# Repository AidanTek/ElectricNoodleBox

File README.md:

# ElectricNoodleBox
Open Source Hardware from/with Electric Noodle Box

This repository hosts a number of hardware projects that are at various stages of completion, for documentation and further info, please visit this page - [Modular Series Overview](https://electricnoodlebox.com/tutorials/modular-series-overview/). Generally speaking, if the docs don't exist then the project probably isn't ready to go! I welcome comments from anyone, whether you are starting out and need better supporting docs, or you are an experienced engineer and think my designs are awful! ;) 

The Electric Noodle Box Modular Series circuits are [open source hardware](https://www.oshwa.org/definition/) designs released under the [CERN-OSH-W](https://ohwr.org/cern_ohl_w_v2.txt) license. The aim is to help you learn how to build electronic instruments, and to make building more accessible. I chose to release designs this way in recognition of my own learning, made possible by the rich history of DIY sound electronics available in the public domain. Open source hardware allows for continued dialogue in making and inventing and I want you to be able to take part in the conversation, whatever point you are at in your learning journey.

All hardware files are produced in Eagle. The free version of Eagle will allow you to browse, modify (most designs, there are some limitations) and create GERBERs for production - PCB fabs such as [OSHPark](https://oshpark.com/) will take Eagle files directly. I have also provided the ENB Eagle library to maintain parts that might not be included in the standard libraries. Please let me know by raising an issue if you have any problems accessing or opening these files.

I recognise there are some issues with Eagle and open-source due to the limitations of the free version. I believe it is possible to convert Eagle .brd .sch and .lbr files over to KiCAD - but this is a big task. I would welcome support if someone has experience and wants to take this on.

## License

The CERN-OSH-W allows you to use all source files in this repository in any way you wish. It requires that any resources you use from here remain as open source, even if used in a wider project that is otherwise closed. 

I chose this license so you are not restricted in your use of the source contentno matter what your plans are. I am interested in what you do with these designs however as I want them to stimulate learning and dialogue. My personal request is that you consider sharing ideas if choose to make, modify or integrate content from this source, and consider referencing me or Electric Noodle Box for the many hours I have spent developing this resource! :)

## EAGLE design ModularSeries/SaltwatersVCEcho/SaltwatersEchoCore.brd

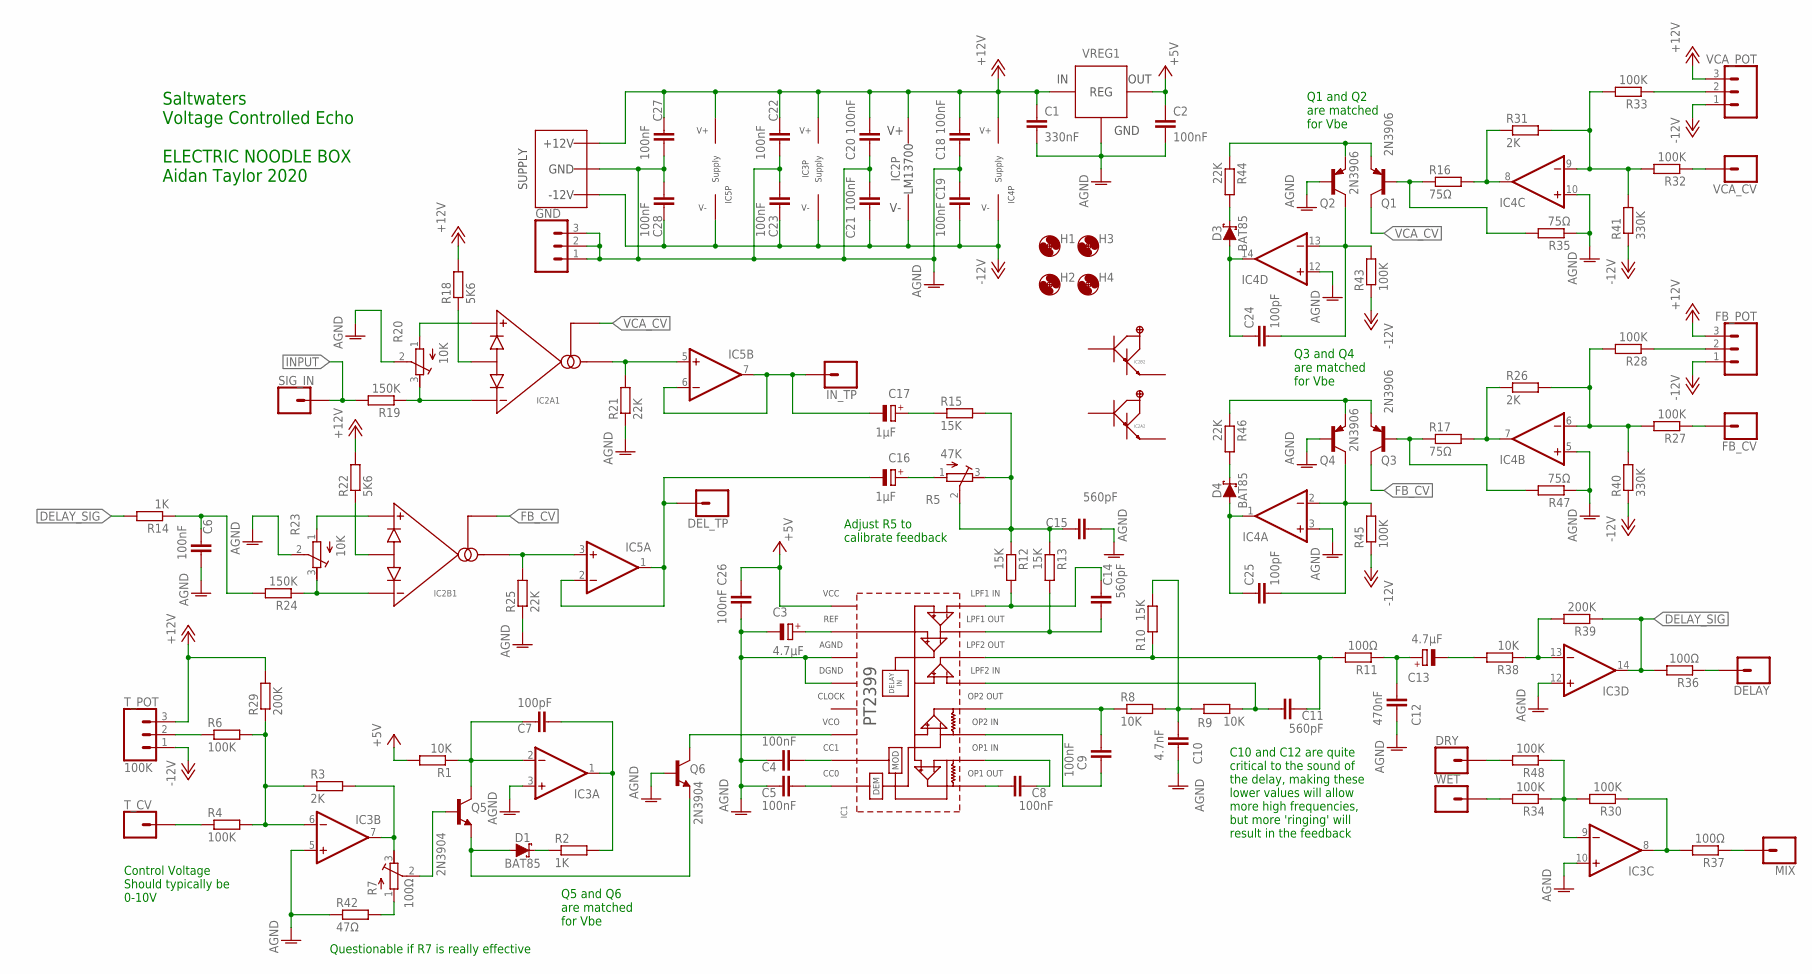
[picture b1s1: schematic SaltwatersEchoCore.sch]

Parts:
C1: 330nF; C050-025X075
C2, C4, C5, C6, C8, C9, C18, C19, C20, C21, C22, C23, C26, C27, C28: 100nF; C050-025X075
C3, C13: 4.7µF; E2-5
C7, C24, C25: 100pF; C050-025X075
C10: 4.7nF; C050-025X075
C11, C14, C15: 560pF; C050-025X075
C12: 470nF; C050-025X075
C16, C17: 1µF; E2-5
D1, D3, D4: BAT85; DO35-7
DELAY: 1XWIREPAD; 1X01
DEL_TP: 1XWIREPAD; 1X01
DRY: 1XWIREPAD; 1X01
FB_CV: 1XWIREPAD; 1X01
FB_POT: 3XWIREPAD; 1X03
GND: 3XWIREPAD; 1X03
H1, H2, H3, H4: MOUNT-HOLE3.2; 3,2
IC1: PT2399DIL16; DIL16
IC2: LM13700DIL; DIL16
IC3, IC4: TL0X4DIL; DIL14
IC5: TL0X2DIL; DIL08
IN_TP: 1XWIREPAD; 1X01
MIX: 1XWIREPAD; 1X01
Q1, Q2, Q3, Q4: 2N3906; TO92
Q5, Q6: 2N3904; TO92
R1, R8, R9, R38: 10K; 0207/10
R2, R14: 1K; 0207/10
R3, R26, R31: 2K; 0207/10
R4, R6, R27, R28, R30, R32, R33, R34, R43, R45, R48: 100K; 0207/10
R5: 47K; RTRIM3296W
R7: 100Ω; RTRIM3296W
R10, R12, R13, R15: 15K; 0207/10
R11, R36, R37: 100Ω; 0207/10
R16, R17, R35, R47: 75Ω; 0207/10
R18, R22: 5K6; 0207/10
R19, R24: 150K; 0207/10
R20, R23: 10K; RTRIM3296W
R21, R25, R44, R46: 22K; 0207/10
R29, R39: 200K; 0207/10
R40, R41: 330K; 0207/10
R42: 47Ω; 0207/10
SIG_IN: 1XWIREPAD; 1X01
T_CV: 1XWIREPAD; 1X01
T_POT: 100K; 1X03
VCA_CV: 1XWIREPAD; 1X01
VCA_POT: 3XWIREPAD; 1X03
VREG1: L78L05TO92; TO92
WET: 1XWIREPAD; 1X01
WP1: COMBO_SUPPLY_HEADER; COMBINED_POWER

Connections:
+5V: C2.1, C26.1, IC1.1 (VCC), R1.2, VREG1.1 (VOUT)
+12V: C1.1, C18.2, C20.2, C22.2, C27.2, FB_POT.3, IC2.11 (V+), IC3.4 (V+), IC4.4 (V+), IC5.8 (V+), R18.2, R22.2, R29.2, T_POT.3, VCA_POT.3, VREG1.3 (VIN), WP1.V+1 (V++), WP1.V+2 (V++), WP1.V+3 (V++)
-12V: C19.1, C21.1, C23.1, C28.1, FB_POT.1, IC2.6 (V-), IC3.11 (V-), IC4.11 (V-), IC5.4 (V-), R40.1, R41.1, R43.1, R45.1, T_POT.1, VCA_POT.1, WP1.V-1 (V--), WP1.V-2 (V--), WP1.V-3 (V--)
AGND: C1.2, C2.2, C3.-, C4.2, C5.2, C6.2, C10.1, C12.1, C15.2, C18.1, C19.2, C20.1, C21.2, C22.1, C23.2, C26.2, C27.1, C28.2, GND.1, GND.2, GND.3, IC1.3 (AGND), IC1.4 (DGND), IC3.3 (+IN), IC3.5 (+IN), IC3.10 (+IN), IC3.12 (+IN), IC4.3 (+IN), IC4.5 (+IN), IC4.10 (+IN), IC4.12 (+IN), Q2.2 (B), Q4.2 (B), Q6.2 (B), R20.2 (S), R21.1, R23.2 (S), R25.1, R35.1, R42.1, R47.1, VREG1.2 (GND), WP1.GND1 (AGND), WP1.GND2 (AGND), WP1.GND3 (AGND), WP1.GND4 (AGND), WP1.GND5 (AGND), WP1.GND6 (AGND), WP1.GND7 (AGND), WP1.GND8 (AGND)
DELAY_SIG: IC3.14 (OUT), R14.2, R36.2, R39.1
FB_CV: IC2.16 (AMPBIAS), Q3.1 (C)
FB_RTN: C16.-, DEL_TP.1, IC5.1 (OUT), IC5.2 (-IN)
INPUT: R19.2, SIG_IN.1
unnamed: C3.+, IC1.2 (REF)
unnamed: C4.1, IC1.7 (CC1)
unnamed: C5.1, IC1.8 (CC0)
unnamed: IC1.6 (VCO), Q6.1 (C)
unnamed: C7.2, IC3.2 (-IN), Q5.1 (C), R1.1
unnamed: C7.1, IC3.1 (OUT), R2.2
unnamed: D1.A, Q5.3 (E), Q6.3 (E)
unnamed: C6.1, R14.1, R24.2
unnamed: D1.C, R2.1
unnamed: IC3.7 (OUT), R3.2, R7.3 (E)
unnamed: Q5.2 (B), R7.2 (S)
unnamed: R4.1, T_CV.1
unnamed: IC3.6 (-IN), R3.1, R4.2, R6.2, R29.1
unnamed: R6.1, T_POT.2
unnamed: C8.1, IC1.10 (OP1_IN)
unnamed: C8.2, IC1.9 (OP1_OUT)
unnamed: C9.1, IC1.11 (OP2_IN)
unnamed: C9.2, IC1.12 (OP2_OUT), R8.1
unnamed: C10.2, R8.2, R9.2, R10.1
unnamed: C11.2, IC1.13 (LPF2_IN), R9.1
unnamed: C11.1, IC1.14 (LPF2_OUT), R10.2, R11.2
unnamed: Q1.2 (B), R16.1, R35.2
unnamed: C12.2, C13.+, R11.1
unnamed: C14.1, IC1.16 (LPF1_IN), R12.2
unnamed: C14.2, IC1.15 (LPF1_OUT), R13.2
unnamed: C15.1, R5.2 (S), R5.3 (E), R12.1, R13.1, R15.2
unnamed: C17.+, R15.1
unnamed: C16.+, R5.1 (A)
unnamed: IC2.4 (AMP-), R19.1, R20.3 (E)
unnamed: IC2.3 (AMP+), R20.1 (A)
unnamed: IC4.7 (OUT), R17.2, R26.1
unnamed: IC2.2 (DIODES), R18.1
unnamed: IC2.5 (AMPOUT), IC5.5 (+IN), R21.2
unnamed: C17.-, IC5.6 (-IN), IC5.7 (OUT), IN_TP.1
unnamed: DELAY.1, R36.1
unnamed: IC2.15 (DIODES), R22.1
unnamed: IC2.13 (AMP-), R23.3 (E), R24.1
unnamed: IC2.14 (AMP+), R23.1 (A)
unnamed: IC4.6 (-IN), R26.2, R27.2, R28.2, R40.2
unnamed: IC2.12 (AMPOUT), IC5.3 (+IN), R25.2
unnamed: Q3.2 (B), R17.1, R47.2
unnamed: DRY.1, R48.2
unnamed: FB_CV.1, R27.1
unnamed: IC4.8 (OUT), R16.2, R31.1
unnamed: FB_POT.2, R28.1
unnamed: IC4.9 (-IN), R31.2, R32.2, R33.2, R41.2
unnamed: C24.1, D3.A, IC4.14 (OUT)
unnamed: C24.2, IC4.13 (-IN), Q2.1 (C), R43.2
unnamed: R32.1, VCA_CV.1
unnamed: R33.1, VCA_POT.2
unnamed: C13.-, R38.2
unnamed: R34.2, WET.1
unnamed: MIX.1, R37.1
unnamed: R7.1 (A), R42.2
unnamed: IC3.9 (-IN), R30.2, R34.1, R48.1
unnamed: IC3.8 (OUT), R30.1, R37.2
unnamed: D3.C, R44.2
unnamed: Q1.3 (E), Q2.3 (E), R44.1
unnamed: IC3.13 (-IN), R38.1, R39.2
unnamed: C25.2, IC4.2 (-IN), Q4.1 (C), R45.2
unnamed: C25.1, D4.A, IC4.1 (OUT)
unnamed: D4.C, R46.2
unnamed: Q3.3 (E), Q4.3 (E), R46.1
VCA_CV: IC2.1 (AMPBIAS), Q1.1 (C)

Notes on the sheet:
Control Voltage Should typically be 0-10V
Saltwaters Voltage Controlled Echo ELECTRIC NOODLE BOX Aidan Taylor 2020
Q1 and Q2 are matched for Vbe
Q3 and Q4 are matched for Vbe
Q5 and Q6 are matched for Vbe
Adjust R5 to calibrate feedback
Questionable if R7 is really effective
C10 and C12 are quite critical to the sound of the delay, making these lower values will allow more high frequencies, but more 'ringing' will result in the feedback

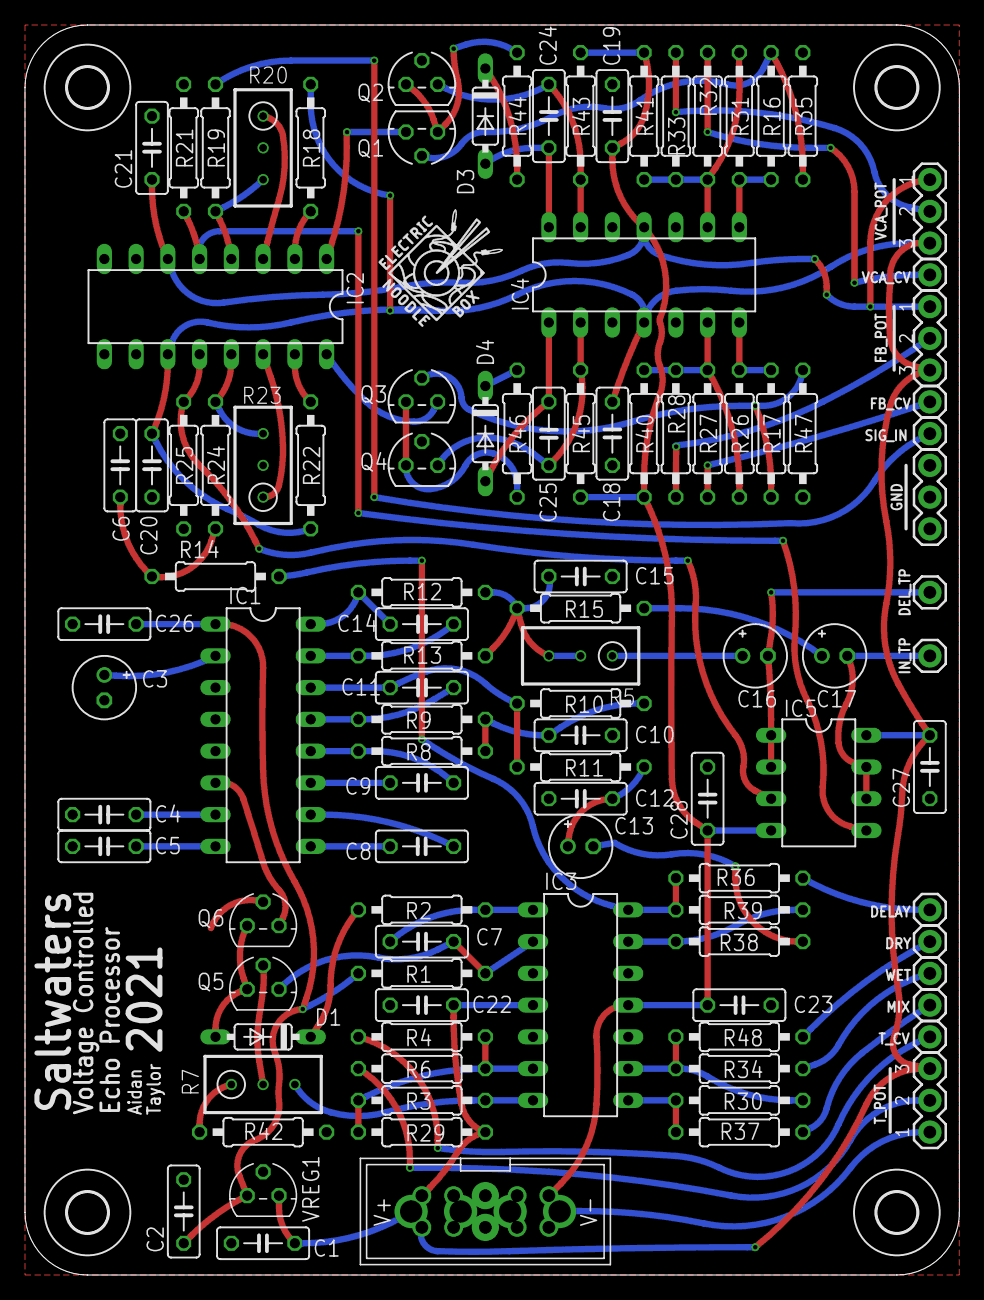
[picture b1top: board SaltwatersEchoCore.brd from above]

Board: 2 copper layers, 74.8 x 100.0 mm, 112 parts (1 on the bottom side), 72 nets.

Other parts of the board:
U$1, U$2: LOGO10X10

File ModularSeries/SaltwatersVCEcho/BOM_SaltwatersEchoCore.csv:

Qty,Value,Package,Parts,Description,RETAILER,CATALOGUE
,,,,,,
9,100K,0207/10,"R4, R5, R6, R27, R28, R32, R33, R43, R45","RESISTOR, European symbol",Farnell,2329853
5,100Ω,0207/10,"R30, R34, R36, R37, R48","RESISTOR, European symbol",Farnell,2329854
5,10K,0207/10,"R8, R9, R35, R38, R47","RESISTOR, European symbol",Farnell,2329855
2,150K,0207/10,"R19, R24","RESISTOR, European symbol",Farnell,2329871
5,15K,0207/10,"R10, R12, R13, R14, R15","RESISTOR, European symbol",Farnell,2329873
3,1K,0207/10,"R2, R16, R17","RESISTOR, European symbol",Farnell,2329885
2,200K,0207/10,"R29, R39","RESISTOR, European symbol",Farnell,2329895
4,22K,0207/10,"R21, R25, R44, R46","RESISTOR, European symbol",Farnell,2329901
3,2K,0207/10,"R3, R26, R31","RESISTOR, European symbol",Farnell,2329911
2,330K,0207/10,"R40, R41","RESISTOR, European symbol",Farnell,9341765
1,47K,0207/10,R1,"RESISTOR, European symbol",Farnell,2329944
1,47Ω,0207/10,R42,"RESISTOR, European symbol",Farnell,2329945
2,5K7,0207/10,"R18, R22","RESISTOR, European symbol",Farnell,2329958
1,7K5,0207/10,R11,"RESISTOR, European symbol",Farnell,2329974
1,100Ω,RTRIM3296W,R7,Trimm resistor,Farnell,9353500
2,10K,RTRIM3296W,"R20, R23",Trimm resistor,Farnell,9353186
,,,,,,
14,100nF,C050-025X075,"C2, C4, C5, C8, C9, C18, C19, C20, C21, C22, C23, C26, C27, C28","CAPACITOR, European symbol",Farnell,2797801
3,100pF,C050-025X075,"C7, C24, C25","CAPACITOR, European symbol",Farnell,1141765
1,10nF,C050-025X075,C12,"CAPACITOR, European symbol",Farnell,1141772
1,330nF,C050-025X075,C1,"CAPACITOR, European symbol",Farnell,2309021
1,4.7nF,C050-025X075,C10,"CAPACITOR, European symbol",Farnell,2860131
2,4.7µF,E2-5,"C3, C13","POLARIZED CAPACITOR, European symbol",Farnell,9451234
3,560pF,C050-025X075,"C11, C14, C15","CAPACITOR, European symbol",Farnell,2990777
3,1µF,E2-5,"C6, C16, C17","POLARIZED CAPACITOR, European symbol",Farnell,1870979
,,,,,,
1,L78L05,TO92,VREG1,5V Regulator TO-92,Farnell,3335817
2,2N3904,TO92,"Q5, Q6",NPN TRANSISTOR,Farnell,1574370
4,2N3906,TO92,"Q1, Q2, Q3, Q4",PNP Transistor,Farnell,1574372
4,BAT85,DO35-7,"D1, D2, D3, D4",BAT85 Schottky Diode,Farnell,2889133
1,LM13700,DIL16,IC2,Dual Transconductance Amplifier with Darlington Buffer,Farnell,3118206
1,TL082,DIL08,IC5,Dual Operational Amplifier,Farnell,1103189
2,TL084,DIL14,"IC3, IC4",Quad Operational Amplifier,Farnell,3117825
1,PT2399DIL16,DIL16,IC1,Echo Processor DIP,Tayda,A-043
,,,,,,
3,Pin Header,Pin Header,,8way 1row 2.54mm Header Pin,Farnell,2856626
1,Power Header,,WP1,10 way Shrouded IDC,Farnell,2843527
,,,,,,
3,B100K,,"T_POT, FB_POT, VCA_POT",Taiwan Alpha 16mm (panel part),Rapid,65-0756
2,B10K,,"T_CV, FB_CV",Taiwan Alpha 16mm (panel part),Rapid,65-0753
6,Banana or Jack Patch Point,1X01,"DELAY, FB_CV, MIX, SIG_IN, T_CV, VCA_CV",Banana or Jack patch point (panel part),Farnell,1698951

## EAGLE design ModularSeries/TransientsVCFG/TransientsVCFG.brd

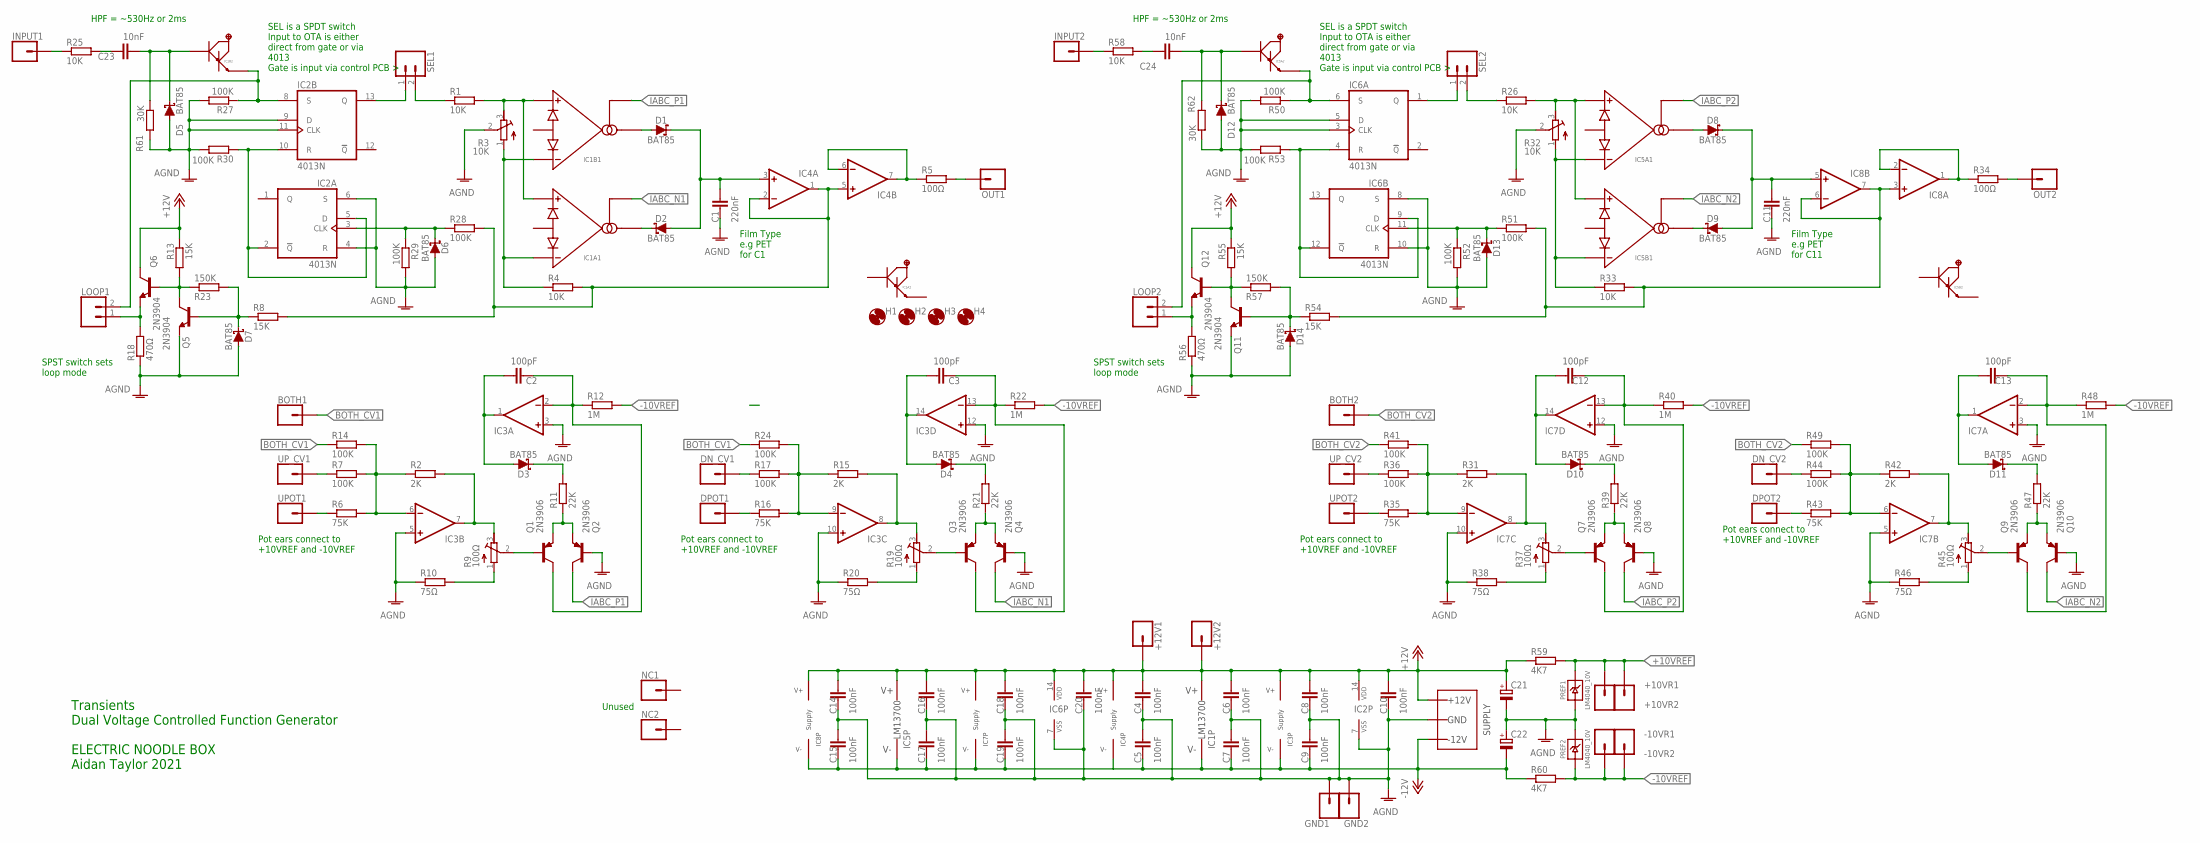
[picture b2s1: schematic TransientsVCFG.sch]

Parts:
+10VR1, +10VR2, +12V1, +12V2: 1XWIREPAD; 1X01
-10VR1, -10VR2: 1XWIREPAD; 1X01
BOTH1, BOTH2: 1XWIREPAD; 1X01
C1, C11: 220nF; C050-025X075
C2, C3, C12, C13: 100pF; C050-025X075
C4, C5, C6, C7, C8, C9, C10, C14, C15, C16, C17, C18, C19, C20: 100nF; C050-025X075
C21, C22: CPOL-EUE2.5-6; E2,5-6
C23, C24: 10nF; C050-025X075
D1, D2, D3, D4, D5, D6, D7, D8, D9, D10, D11, D12, D13, D14: BAT85; DO35-7
DN_CV1, DN_CV2: 1XWIREPAD; 1X01
DPOT1, DPOT2: 1XWIREPAD; 1X01
GND1, GND2: 1XWIREPAD; 1X01
H1, H2, H3, H4: MOUNT-HOLE3.2; 3,2
IC1, IC5: LM13700DIL; DIL16
IC2, IC6: 4013N; DIL14
IC3, IC7: TL0X4DIL; DIL14
IC4, IC8: TL0X2DIL; DIL08
INPUT1, INPUT2: 1XWIREPAD; 1X01
LOOP1, LOOP2: 2XWIREPAD; 1X02
NC1, NC2: 1XWIREPAD; 1X01
OUT1, OUT2: 1XWIREPAD; 1X01
PREF1, PREF2: LM4040_10V; TO92
Q1, Q2, Q3, Q4, Q7, Q8, Q9, Q10: 2N3906; TO92
Q5, Q6, Q11, Q12: 2N3904; TO92
R1, R4, R25, R26, R33, R58: 10K; 0207/10
R2, R15, R31, R42: 2K; 0207/10
R3, R32: 10K; RTRIM3296W
R5, R34: 100Ω; 0207/10
R6, R16, R35, R43: 75K; 0207/10
R7, R14, R17, R24, R27, R28, R29, R30, R36, R41, R44, R49, R50, R51, R52, R53: 100K; 0207/10
R8, R13, R54, R55: 15K; 0207/10
R9, R19, R37, R45: 100Ω; RTRIM3296W
R10, R20, R38, R46: 75Ω; 0207/10
R11, R21, R39, R47: 22K; 0207/10
R12, R22, R40, R48: 1M; 0207/10
R18, R56: 470Ω; 0207/10
R23, R57: 150K; 0207/10
R59, R60: 4K7; 0207/10
R61, R62: 30K; 0207/10
SEL1, SEL2: 2XWIREPAD; 1X02
UPOT1, UPOT2: 1XWIREPAD; 1X01
UP_CV1, UP_CV2: 1XWIREPAD; 1X01
WP1: COMBO_SUPPLY_HEADER; COMBINED_POWER

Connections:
+10VREF: +10VR1.1, +10VR2.1, PREF1.2 (CATHODE), R59.2
+12V: +12V1.1, +12V2.1, C4.1, C6.1, C8.1, C10.1, C14.1, C16.1, C18.1, C20.1, C21.+, IC1.11 (V+), IC2.14 (VDD), IC3.4 (V+), IC4.8 (V+), IC5.11 (V+), IC6.14 (VDD), IC7.4 (V+), IC8.8 (V+), Q6.1 (C), Q12.1 (C), R13.1, R55.1, R59.1, WP1.V+1 (V++), WP1.V+2 (V++), WP1.V+3 (V++)
-10VREF: -10VR1.1, -10VR2.1, PREF2.3 (ANODE), R12.2, R22.2, R40.2, R48.2, R60.2
-12V: C5.2, C7.2, C9.2, C15.2, C17.2, C19.2, C22.-, IC1.6 (V-), IC3.11 (V-), IC4.4 (V-), IC5.6 (V-), IC7.11 (V-), IC8.4 (V-), R60.1, WP1.V-1 (V--), WP1.V-2 (V--), WP1.V-3 (V--)
AGND: C1.2, C4.2, C5.1, C6.2, C7.1, C8.2, C9.1, C10.2, C11.2, C14.2, C15.1, C16.2, C17.1, C18.2, C19.1, C20.2, C21.-, C22.+, D5.A, D6.A, D7.A, D12.A, D13.A, D14.A, GND1.1, GND2.1, IC2.4 (R), IC2.6 (S), IC2.7 (VSS), IC2.9 (D), IC2.11 (CLK), IC3.3 (+IN), IC3.5 (+IN), IC3.10 (+IN), IC3.12 (+IN), IC6.3 (CLK), IC6.5 (D), IC6.7 (VSS), IC6.8 (S), IC6.10 (R), IC7.3 (+IN), IC7.5 (+IN), IC7.10 (+IN), IC7.12 (+IN), PREF1.3 (ANODE), PREF2.2 (CATHODE), Q2.2 (B), Q4.2 (B), Q5.3 (E), Q8.2 (B), Q10.2 (B), Q11.3 (E), R3.2 (S), R10.1, R18.1, R20.1, R27.2, R29.2, R30.2, R32.2 (S), R38.1, R46.1, R50.2, R52.2, R53.2, R56.1, R61.2, R62.2, WP1.GND1 (AGND), WP1.GND2 (AGND), WP1.GND3 (AGND), WP1.GND4 (AGND), WP1.GND5 (AGND), WP1.GND6 (AGND), WP1.GND7 (AGND), WP1.GND8 (AGND)
BOTH_CV1: BOTH1.1, R14.1, R24.1
BOTH_CV2: BOTH2.1, R41.1, R49.1
IABC_N1: IC1.1 (AMPBIAS), Q4.1 (C)
IABC_N2: IC5.16 (AMPBIAS), Q10.1 (C)
IABC_P1: IC1.16 (AMPBIAS), Q2.1 (C)
IABC_P2: IC5.1 (AMPBIAS), Q8.1 (C)
unnamed: IC1.3 (AMP+), IC1.14 (AMP+), R1.2, R3.3 (E)
unnamed: D1.A, IC1.12 (AMPOUT)
unnamed: C1.1, D1.C, D2.A, IC4.3 (+IN)
unnamed: IC4.1 (OUT), IC4.2 (-IN), IC4.5 (+IN), R4.2, R8.2, R28.2
unnamed: D2.C, IC1.5 (AMPOUT)
unnamed: IC4.6 (-IN), IC4.7 (OUT), R5.1
unnamed: IC1.4 (AMP-), IC1.13 (AMP-), R3.1 (A), R4.1
unnamed: IC3.6 (-IN), R2.1, R6.2, R7.2, R14.2
unnamed: IC3.7 (OUT), R2.2, R9.3 (E)
unnamed: R9.1 (A), R10.2
unnamed: Q1.2 (B), R9.2 (S)
unnamed: Q1.3 (E), Q2.3 (E), R11.1
unnamed: C2.1, D3.A, IC3.1 (OUT)
unnamed: C2.2, IC3.2 (-IN), Q1.1 (C), R12.1
unnamed: D3.C, R11.2
unnamed: IC5.3 (AMP+), IC5.14 (AMP+), R26.2, R32.3 (E)
unnamed: C11.1, D8.C, D9.A, IC8.5 (+IN)
unnamed: R7.1, UP_CV1.1
unnamed: OUT1.1, R5.2
unnamed: IC3.9 (-IN), R15.1, R16.2, R17.2, R24.2
unnamed: R6.1, UPOT1.1
unnamed: IC3.8 (OUT), R15.2, R19.3 (E)
unnamed: R19.1 (A), R20.2
unnamed: Q3.2 (B), R19.2 (S)
unnamed: Q3.3 (E), Q4.3 (E), R21.1
unnamed: C3.1, D4.A, IC3.14 (OUT)
unnamed: C3.2, IC3.13 (-IN), Q3.1 (C), R22.1
unnamed: IC1.9 (BUFF_OUT), IC2.8 (S), LOOP1.2, R27.1
unnamed: D4.C, R21.2
unnamed: Q5.1 (C), Q6.2 (B), R13.2, R23.1
unnamed: DN_CV1.1, R17.1
unnamed: DPOT1.1, R16.1
unnamed: R1.1, SEL1.2
unnamed: IC2.13 (Q), SEL1.1
unnamed: IC8.3 (+IN), IC8.6 (-IN), IC8.7 (OUT), R33.2, R51.2, R54.2
unnamed: INPUT1.1, R25.1
unnamed: IC2.2 (!Q), IC2.5 (D), IC2.10 (R), R30.1
unnamed: LOOP1.1, Q6.3 (E), R18.2
unnamed: D7.C, Q5.2 (B), R8.1, R23.2
unnamed: C23.2, D5.C, IC1.10 (BUFF_IN), R61.1
unnamed: D6.C, IC2.3 (CLK), R28.1, R29.1
unnamed: D8.A, IC5.5 (AMPOUT)
unnamed: D9.C, IC5.12 (AMPOUT)
unnamed: IC5.4 (AMP-), IC5.13 (AMP-), R32.1 (A), R33.1
unnamed: IC8.1 (OUT), IC8.2 (-IN), R34.1
unnamed: IC7.9 (-IN), R31.1, R35.2, R36.2, R41.2
unnamed: IC7.8 (OUT), R31.2, R37.3 (E)
unnamed: R37.1 (A), R38.2
unnamed: Q7.2 (B), R37.2 (S)
unnamed: Q7.3 (E), Q8.3 (E), R39.1
unnamed: C12.1, D10.A, IC7.14 (OUT)
unnamed: C12.2, IC7.13 (-IN), Q7.1 (C), R40.1
unnamed: R36.1, UP_CV2.1
unnamed: R35.1, UPOT2.1
unnamed: OUT2.1, R34.2
unnamed: IC7.6 (-IN), R42.1, R43.2, R44.2, R49.2
unnamed: IC7.7 (OUT), R42.2, R45.3 (E)
unnamed: R45.1 (A), R46.2
unnamed: Q9.2 (B), R45.2 (S)
unnamed: Q9.3 (E), Q10.3 (E), R47.1
unnamed: C13.1, D11.A, IC7.1 (OUT)
unnamed: C13.2, IC7.2 (-IN), Q9.1 (C), R48.1
unnamed: DN_CV2.1, R44.1
unnamed: DPOT2.1, R43.1
unnamed: IC6.4 (R), IC6.9 (D), IC6.12 (!Q), R53.1
unnamed: IC5.8 (BUFF_OUT), IC6.6 (S), LOOP2.2, R50.1
unnamed: R26.1, SEL2.2
unnamed: IC6.1 (Q), SEL2.1
unnamed: D13.C, IC6.11 (CLK), R51.1, R52.1
unnamed: C24.1, R58.2
unnamed: D11.C, R47.2
unnamed: D10.C, R39.2
unnamed: Q11.1 (C), Q12.2 (B), R55.2, R57.1
unnamed: LOOP2.1, Q12.3 (E), R56.2
unnamed: D14.C, Q11.2 (B), R54.1, R57.2
unnamed: INPUT2.1, R58.1
unnamed: C23.1, R25.2
unnamed: C24.2, D12.C, IC5.7 (BUFF_IN), R62.1

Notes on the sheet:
Film Type e.g PET for C1
SEL is a SPDT switch Input to OTA is either direct from gate or via 4013 Gate is input via control PCB >
SPST switch sets loop mode
Film Type e.g PET for C11
Pot ears connect to +10VREF and -10VREF
Unused
HPF = ~530Hz or 2ms
Transients Dual Voltage Controlled Function Generator ELECTRIC NOODLE BOX Aidan Taylor 2021

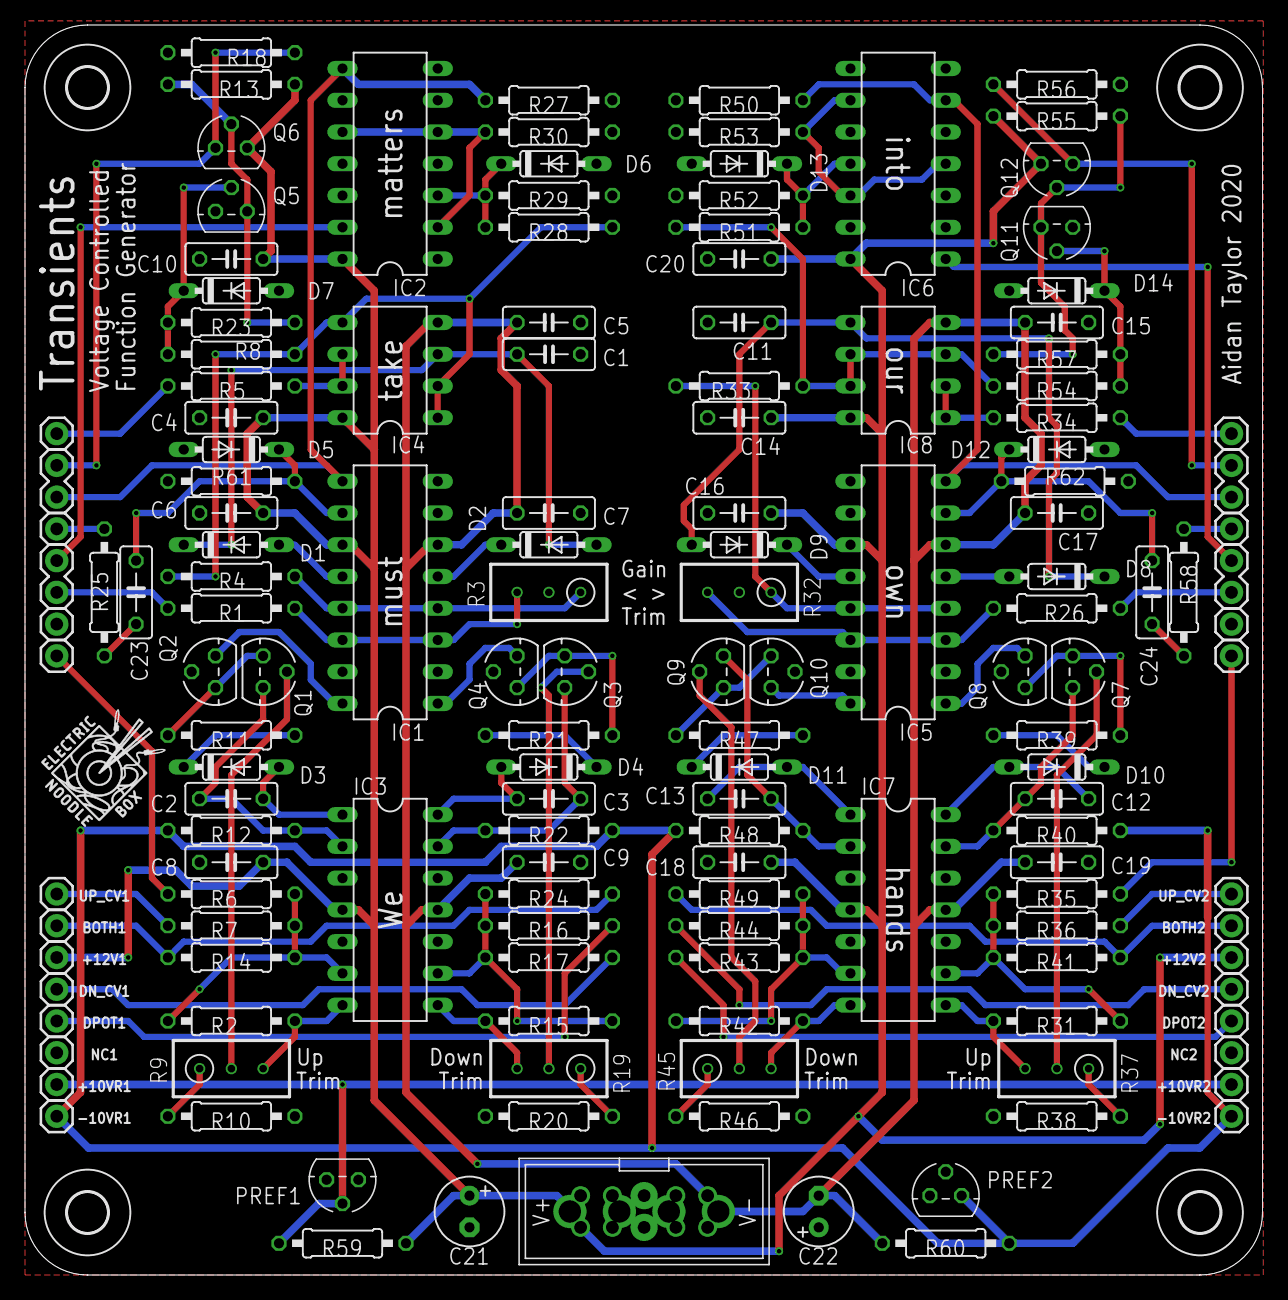
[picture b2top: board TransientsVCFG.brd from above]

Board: 2 copper layers, 99.0 x 100.0 mm, 157 parts (1 on the bottom side), 89 nets.

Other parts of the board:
U$1, U$2: LOGO10X10

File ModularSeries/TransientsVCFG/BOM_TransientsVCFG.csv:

Qty,Value,Package,Parts,Description,CATALOGUE,RETAILER
,,,,,,
20,100K,0207/10,"R7, R12, R14, R17, R22, R24, R27, R28, R29, R30, R36, R40, R41, R44, R48, R49, R50, R51, R52, R53",RESISTOR 1/4W,2329853,Farnell
2,100Ω,0207/10,"R5, R34",RESISTOR 1/4W,2329854,Farnell
6,10K,0207/10,"R1, R4, R25, R26, R33, R58",RESISTOR 1/4W,2329855,Farnell
2,150K,0207/10,"R23, R57",RESISTOR 1/4W,2329871,Farnell
4,15K,0207/10,"R8, R13, R54, R55",RESISTOR 1/4W,2329873,Farnell
4,22K,0207/10,"R11, R21, R39, R47",RESISTOR 1/4W,2329901,Farnell
4,2K,0207/10,"R2, R15, R31, R42",RESISTOR 1/4W,2329911,Farnell
2,30K,0207/10,"R61, R62",RESISTOR 1/4W,2329917,Farnell
2,470Ω,0207/10,"R18, R56",RESISTOR 1/4W,2329942,Farnell
2,4K7,0207/10,"R59, R60",RESISTOR 1/4W,2329945,Farnell
4,47K,0207/10,"R6, R16, R35, R43",RESISTOR 1/4W,2329944,Farnell
4,75Ω,0207/10,"R10, R20, R38, R46",RESISTOR 1/4W,2329973,Farnell
4,100Ω,RTRIM3296W,"R9, R19, R37, R45",Trimm resistor,9353186,Farnell
2,10K,RTRIM3296W,"R3, R32",Trimm resistor,9353186,Farnell
,,,,,,
16,100nF,C050-025X075,"C1, C4, C5, C6, C7, C8, C9, C10, C11, C14, C15, C16, C17, C18, C19, C20","CAPACITOR, European symbol",2797801,Farnell
4,100pF,C050-025X075,"C2, C3, C12, C13","CAPACITOR, European symbol",1141765,Farnell
2,22µF,"E2,5-6","C21, C22","POLARIZED CAPACITOR, European symbol",9451161,Farnell
2,10nF,C050-025X075,"C23, C24","CAPACITOR, European symbol",1131772,Farnell
,,,,,,
14,BAT85,DO35-7,"D1, D2, D3, D4, D5, D6, D7, D8, D9, D10, D11, D12, D13, D14",,2889133,Farnell
4,2N3904,TO92,"Q5, Q6, Q11, Q12",NPN Transistor,1574370,Farnell
8,2N3906,TO92,"Q1, Q2, Q3, Q4, Q7, Q8, Q9, Q10",PNP Transistor,1574372,Farnell
2,LM4040_10V,TO92,"PREF1, PREF2",10V Precision Reference ,3124449,Farnell
2,4013N,DIL14,"IC2, IC6","Dual D FLIP FLOP, set/reset",3119947,Farnell
2,LM13700,DIL16,"IC1, IC5",Dual Transconductance Amplifier with Darlington Buffer,3118206,Farnell
2,TL082,DIL08,"IC4, IC8",Dual Operational Amplifier,1103189,Farnell
2,TL084,DIL14,"IC3, IC7",Quad Operational Amplifier,3117825,Farnell
,,,,,,
1,COMBO_SUPPLY_HEADER,COMBINED_POWER,,10 way Shrouded IDC,2843527,Farnell
4,Pin Header,Pin Header,,8way 1row 2.54mm Header Pin,2856626,Farnell
,,,,,,
10,Banana Connector,,"BOTH1, BOTH2, INPUT1, INPUT2, OUT1, OUT2, DN_CV1, DN_CV2, UP_CV1, UP_CV2",PANEL WIRE ONLY Banana or Jack patch point,1698951,Farnell
4,B10K,,"DN_CV1, DN_CV2, UP_CV1, UP_CV2",PANEL WIRE ONLY Taiwan Alpha 16mm,65-0753,Rapid
4,B100K,,"DPOT1, DPOT2, UPOT1, UPOT2",PANEL WIRE ONLY Taiwan Alpha 16mm,65-0756,Rapid
4,SPDT,,"LOOP1, LOOP2, SEL1, SEL2",PANEL WIRE ONLY SPDT Toggle Switch,9473416,Farnell

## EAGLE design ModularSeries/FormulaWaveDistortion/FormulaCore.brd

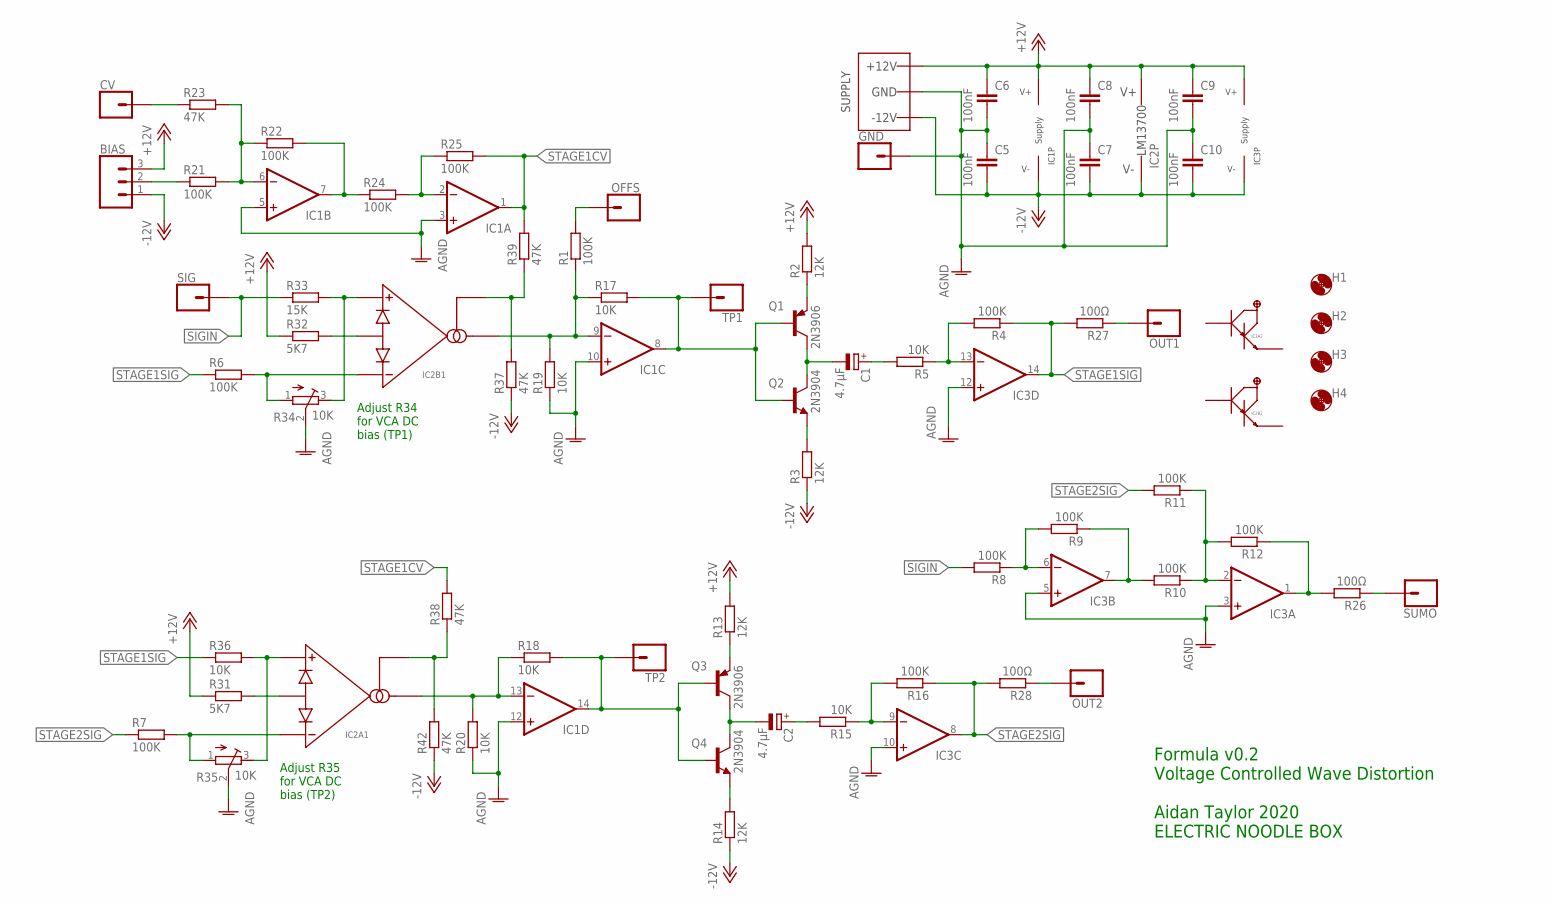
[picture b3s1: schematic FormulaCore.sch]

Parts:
BIAS: 3XWIREPAD; 1X03
C1, C2: 4.7µF; E2,5-5
C5, C6, C7, C8, C9, C10: 100nF; C050-025X075
CV: 1XWIREPAD; 1X01
GND: 1XWIREPAD; 1X01
H1, H2, H3, H4: MOUNT-HOLE3.2; 3,2
IC1, IC3: TL0X4DIL; DIL14
IC2: LM13700DIL; DIL16
OFFS: 1XWIREPAD; 1X01
OUT1, OUT2: 1XWIREPAD; 1X01
Q1, Q3: 2N3906; TO92
Q2, Q4: 2N3904; TO92
R1, R4, R6, R7, R8, R9, R10, R11, R12, R16, R21, R22, R24, R25: 100K; 0207/7
R2, R3, R13, R14: 12K; 0207/7
R5, R15, R17, R18, R19, R20, R36: 10K; 0207/7
R23, R37, R38, R39, R42: 47K; 0207/7
R26, R27, R28: 100Ω; 0207/7
R31, R32: 5K7; 0207/7
R33: 15K; 0207/7
R34, R35: 10K; RTRIM3296W
SIG: 1XWIREPAD; 1X01
SUMO: 1XWIREPAD; 1X01
TP1, TP2: 1XWIREPAD; 1X01
WP1: COMBO_SUPPLY_HEADER; COMBINED_POWER

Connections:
+12V: BIAS.3, C6.1, C8.1, C9.1, IC1.4 (V+), IC2.11 (V+), IC3.4 (V+), R2.2, R13.2, R31.1, R32.1, WP1.V+1 (V++), WP1.V+2 (V++), WP1.V+3 (V++)
-12V: BIAS.1, C5.2, C7.2, C10.2, IC1.11 (V-), IC2.6 (V-), IC3.11 (V-), R3.1, R14.1, R37.1, R42.1, WP1.V-1 (V--), WP1.V-2 (V--), WP1.V-3 (V--)
AGND: C5.1, C6.2, C7.1, C8.2, C9.2, C10.1, GND.1, IC1.3 (+IN), IC1.5 (+IN), IC1.10 (+IN), IC1.12 (+IN), IC3.3 (+IN), IC3.5 (+IN), IC3.10 (+IN), IC3.12 (+IN), R19.1, R20.1, R34.2 (S), R35.2 (S), WP1.GND1 (AGND), WP1.GND2 (AGND), WP1.GND3 (AGND), WP1.GND4 (AGND), WP1.GND5 (AGND), WP1.GND6 (AGND), WP1.GND7 (AGND), WP1.GND8 (AGND)
unnamed: C1.+, R5.2
unnamed: Q1.3 (E), R2.1
unnamed: Q2.3 (E), R3.2
unnamed: C1.-, Q1.1 (C), Q2.1 (C)
unnamed: IC3.13 (-IN), R4.2, R5.1
unnamed: C2.+, R15.2
unnamed: IC3.6 (-IN), R8.1, R9.2
unnamed: IC3.1 (OUT), R12.1, R26.2
unnamed: IC1.8 (OUT), Q1.2 (B), Q2.2 (B), R17.2, TP1.1
unnamed: Q3.3 (E), R13.1
unnamed: C2.-, Q3.1 (C), Q4.1 (C)
unnamed: OFFS.1, R1.2
unnamed: R26.1, SUMO.1
unnamed: IC3.7 (OUT), R9.1, R10.2
unnamed: OUT1.1, R27.1
unnamed: IC3.2 (-IN), R10.1, R11.1, R12.2
unnamed: Q4.3 (E), R14.2
unnamed: OUT2.1, R28.1
unnamed: IC3.9 (-IN), R15.1, R16.2
unnamed: IC1.13 (-IN), IC2.5 (AMPOUT), R18.1, R20.2
unnamed: IC1.9 (-IN), IC2.12 (AMPOUT), R1.1, R17.1, R19.2
unnamed: IC1.14 (OUT), Q3.2 (B), Q4.2 (B), R18.2, TP2.1
unnamed: IC1.6 (-IN), R21.2, R22.1, R23.2
unnamed: IC1.7 (OUT), R22.2, R24.1
unnamed: IC1.2 (-IN), R24.2, R25.1
unnamed: BIAS.2, R21.1
unnamed: CV.1, R23.1
unnamed: IC2.3 (AMP+), R35.3 (E), R36.2
unnamed: IC2.4 (AMP-), R7.2, R35.1 (A)
unnamed: IC2.2 (DIODES), R31.2
unnamed: IC2.15 (DIODES), R32.2
unnamed: IC2.16 (AMPBIAS), R37.2, R39.1
unnamed: IC2.14 (AMP+), R33.2, R34.3 (E)
unnamed: IC2.13 (AMP-), R6.2, R34.1 (A)
unnamed: IC2.1 (AMPBIAS), R38.1, R42.2
SIGIN: R8.2, R33.1, SIG.1
STAGE1CV: IC1.1 (OUT), R25.2, R38.2, R39.2
STAGE1SIG: IC3.14 (OUT), R4.1, R6.1, R27.2, R36.1
STAGE2SIG: IC3.8 (OUT), R7.1, R11.2, R16.1, R28.2

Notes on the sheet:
Adjust R34 for VCA DC bias (TP1)
Formula v0.2 Voltage Controlled Wave Distortion Aidan Taylor 2020 ELECTRIC NOODLE BOX
Adjust R35 for VCA DC bias (TP2)

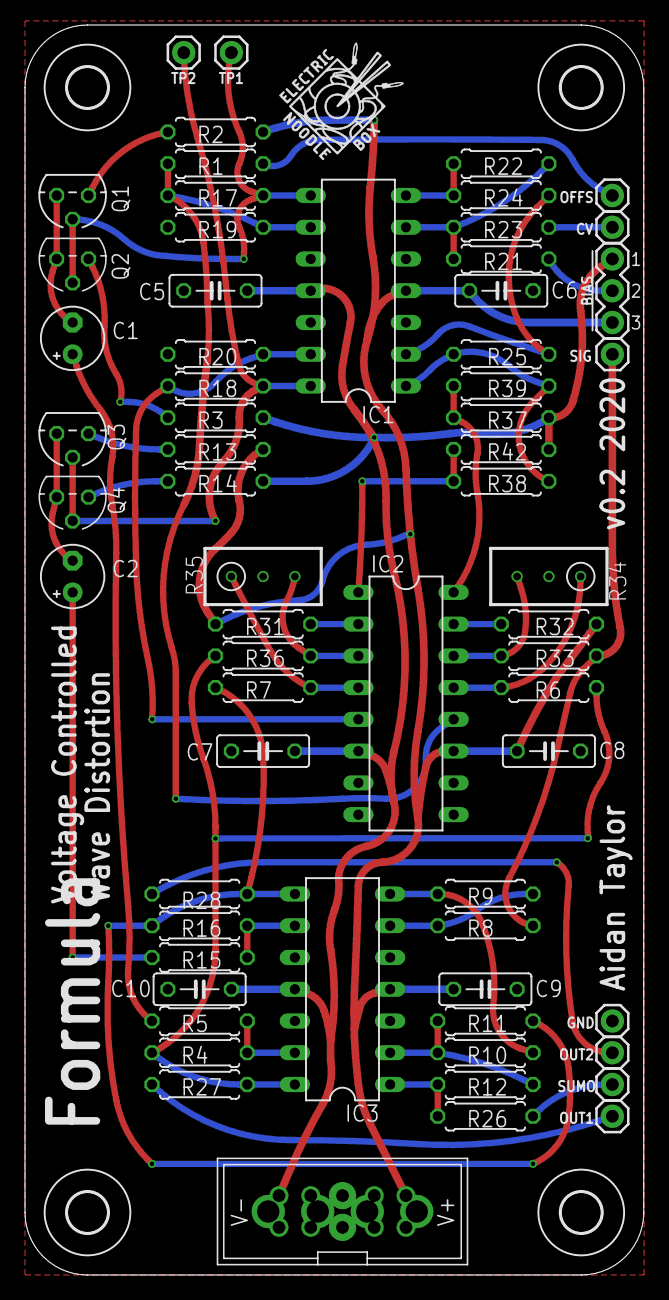
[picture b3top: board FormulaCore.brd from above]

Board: 2 copper layers, 49.5 x 100.0 mm, 70 parts (1 on the bottom side), 42 nets.

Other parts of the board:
U$1, U$2: LOGO10X10

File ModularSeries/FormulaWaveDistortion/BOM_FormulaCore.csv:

Qty,Value,Package,Parts,Description,RETAILER,CATALOGUE
,,,,,,
14,100K,0207/7,"R1, R4, R6, R7, R8, R9, R10, R11, R12, R16, R21, R22, R24, R25","RESISTOR, 1/4W",Farnell,2329853
3,100Ω,0207/7,"R26, R27, R28","RESISTOR, 1/4W",Farnell,2329854
7,10K,0207/7,"R5, R15, R17, R18, R19, R20, R36","RESISTOR, 1/4W",Farnell,2329855
4,12K,0207/7,"R2, R3, R13, R14","RESISTOR, 1/4W",,
1,15K,0207/7,R33,"RESISTOR, 1/4W",Farnell,2329873
5,47K,0207/7,"R23, R37, R38, R39, R42","RESISTOR, 1/4W",Farnell,2329944
2,5K7,0207/7,"R31, R32","RESISTOR, 1/4W",Farnell,2329958
2,10K,RTRIM3296W,"R34, R35",Trimm resistor 3296W,Farnell,9353186
,,,,,,
6,100nF,C050-025X075,"C5, C6, C7, C8, C9, C10","Ceramic / Film CAPACITOR, 5mm",Farnell,2797801
2,4.7µF,"E2,5-5","C1, C2",Electrolytic CAPACITOR,Farnell,2329863
,,,,,,
2,2N3904,TO92,"Q2, Q4",NPN Transistor,Farnell,1574370
2,2N3906,TO92,"Q1, Q3",PNP Transistor,Farnell,1574372
1,LM13700,DIL16,IC2,Dual Transconductance Amplifier with Darlington Buffer,Farnell,3118206
2,TL084,DIL14,"IC1, IC3",Quad Operational Amplifier,Farnell,3005140
,,,,,,
1,COMBO_SUPPLY_HEADER,COMBINED_POWER,WP1,10 way Shrouded IDC,Farnell,2843527
2,Pin Header,Pin Header,,8way 1row 2.54mm Header Pin,Farnell,2856626
,,,,,,
2,B10K Potentiometer,,,PANEL WIRE ONLY Taiwan Alpha 16mm,Rapid,65-0753
1,B100K Potentiometer,,BIAS,PANEL WIRE ONLY Taiwan Alpha 16mm,Rapid,65-0756
7,Banana Connector,,"CV, GND, OFFS, OUT1, OUT2, SIG, SUMO",PANEL WIRE ONLY Banana or Jack patch point,1698951,Farnell
